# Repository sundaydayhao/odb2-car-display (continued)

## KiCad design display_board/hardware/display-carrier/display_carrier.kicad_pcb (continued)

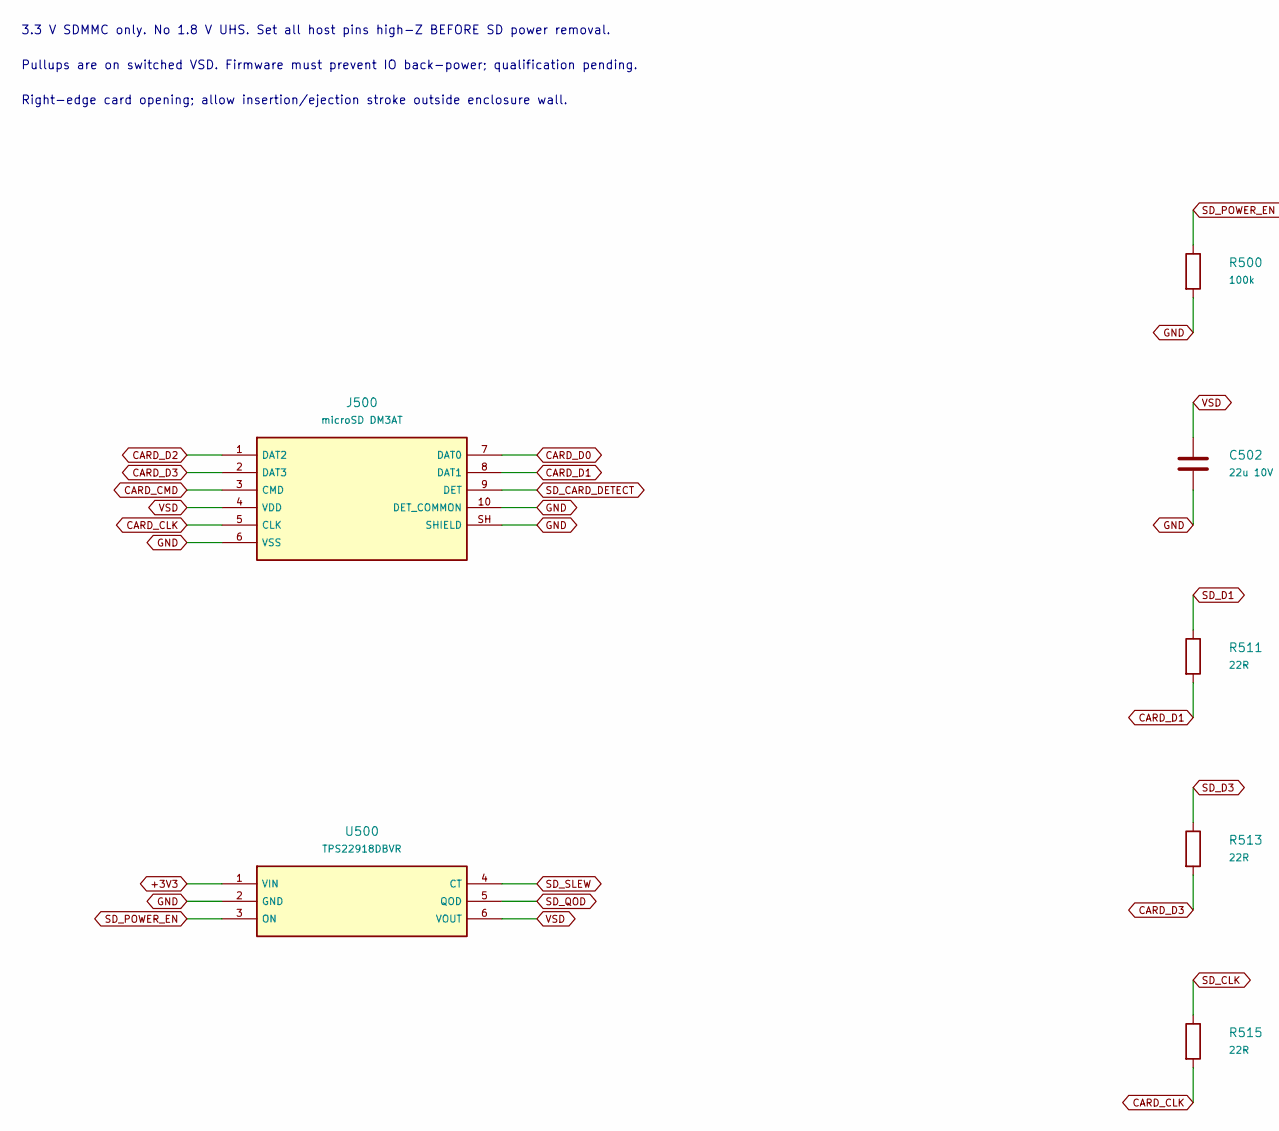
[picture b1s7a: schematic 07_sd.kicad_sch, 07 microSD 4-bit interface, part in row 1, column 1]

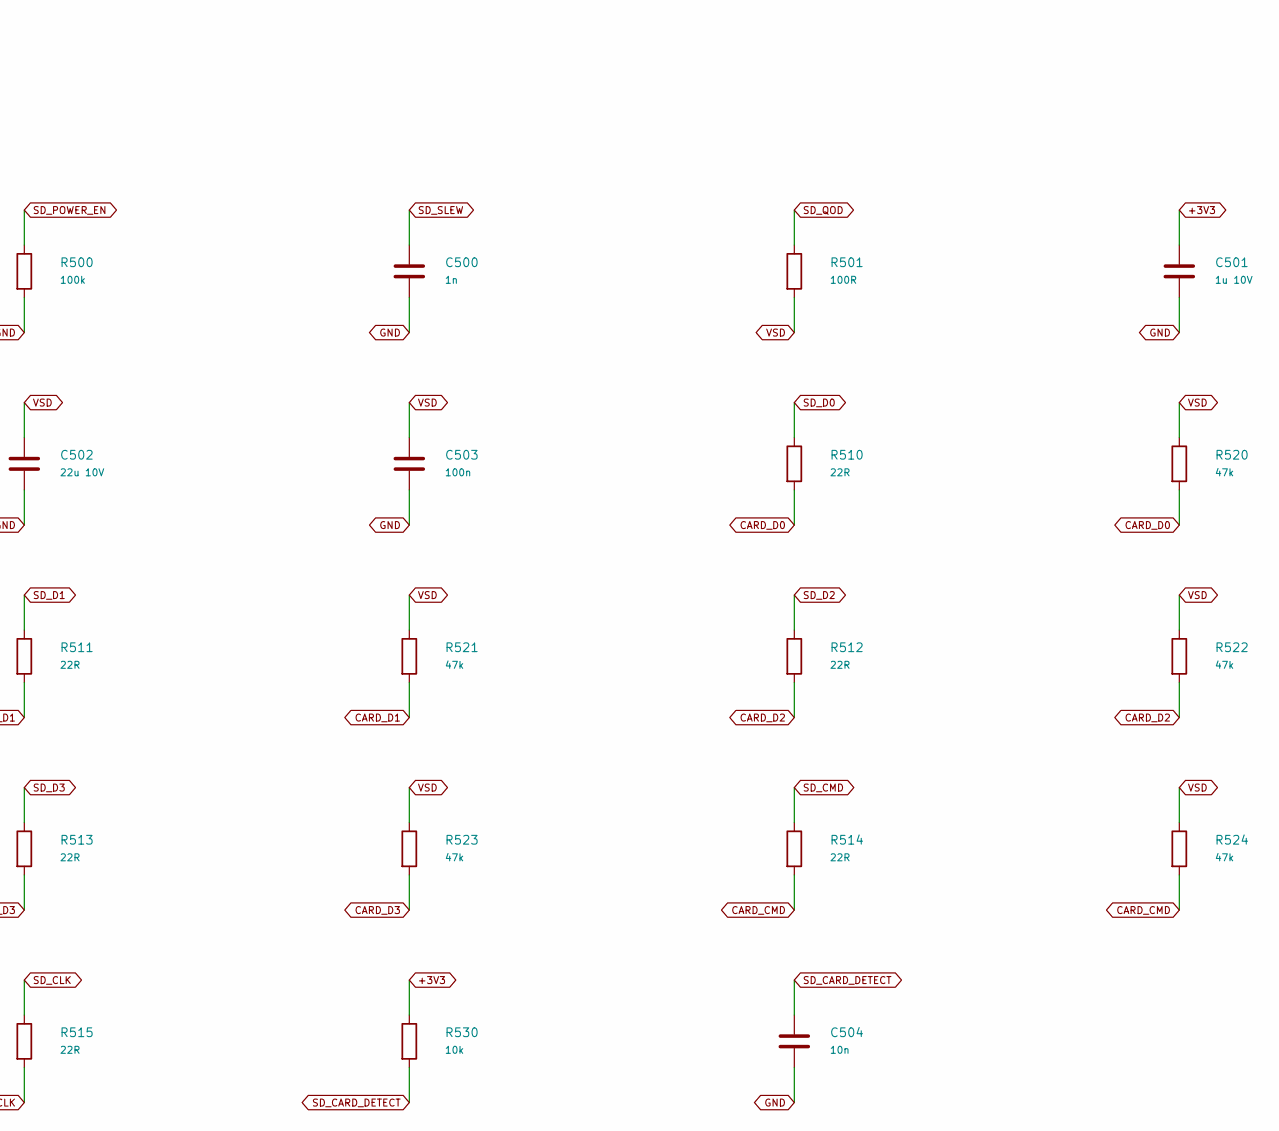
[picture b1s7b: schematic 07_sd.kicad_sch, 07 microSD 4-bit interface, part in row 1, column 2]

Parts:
C500: 1n; C_0402_1005Metric
C501: 1u 10V; C_0603_1608Metric
C502: 22u 10V; C_0805_2012Metric
C503: 100n; C_0402_1005Metric
C504: 10n; C_0603_1608Metric
J500: microSD DM3AT; microSD_HC_Hirose_DM3AT-SF-PEJM5
R500: 100k; R_0402_1005Metric
R501: 100R; R_0603_1608Metric
R510, R511, R512, R513, R514, R515: 22R; R_0402_1005Metric
R520, R521, R522, R523, R524: 47k; R_0402_1005Metric
R530: 10k; R_0402_1005Metric
U500: TPS22918DBVR; SOT-23-6

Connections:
+3V3: C501.1, R530.1, U500.1 (VIN); also elsewhere on the board
CARD_CLK: J500.5 (CLK), R515.2
CARD_CMD: J500.3 (CMD), R514.2, R524.2
CARD_D0: J500.7 (DAT0), R510.2, R520.2
CARD_D1: J500.8 (DAT1), R511.2, R521.2
CARD_D2: J500.1 (DAT2), R512.2, R522.2
CARD_D3: J500.2 (DAT3), R513.2, R523.2
GND: C500.2, C501.2, C502.2, C503.2, C504.2, J500.6 (VSS), J500.10 (DET_COMMON), J500.SH (SHIELD), R500.2, U500.2 (GND); also elsewhere on the board
SD_CARD_DETECT: C504.1, J500.9 (DET), R530.2; also elsewhere on the board
SD_CLK: R515.1; also elsewhere on the board
SD_CMD: R514.1; also elsewhere on the board
SD_D0: R510.1; also elsewhere on the board
SD_D1: R511.1; also elsewhere on the board
SD_D2: R512.1; also elsewhere on the board
SD_D3: R513.1; also elsewhere on the board
SD_POWER_EN: R500.1, U500.3 (ON); also elsewhere on the board
SD_QOD: R501.1, U500.5 (QOD)
SD_SLEW: C500.1, U500.4 (CT)
VSD: C502.1, C503.1, J500.4 (VDD), R501.2, R520.1, R521.1, R522.1, R523.1, R524.1, U500.6 (VOUT)

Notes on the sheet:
3.3 V SDMMC only. No 1.8 V UHS. Set all host pins high-Z BEFORE SD power removal.
Pullups are on switched VSD. Firmware must prevent IO back-power; qualification pending.
Right-edge card opening; allow insertion/ejection stroke outside enclosure wall.

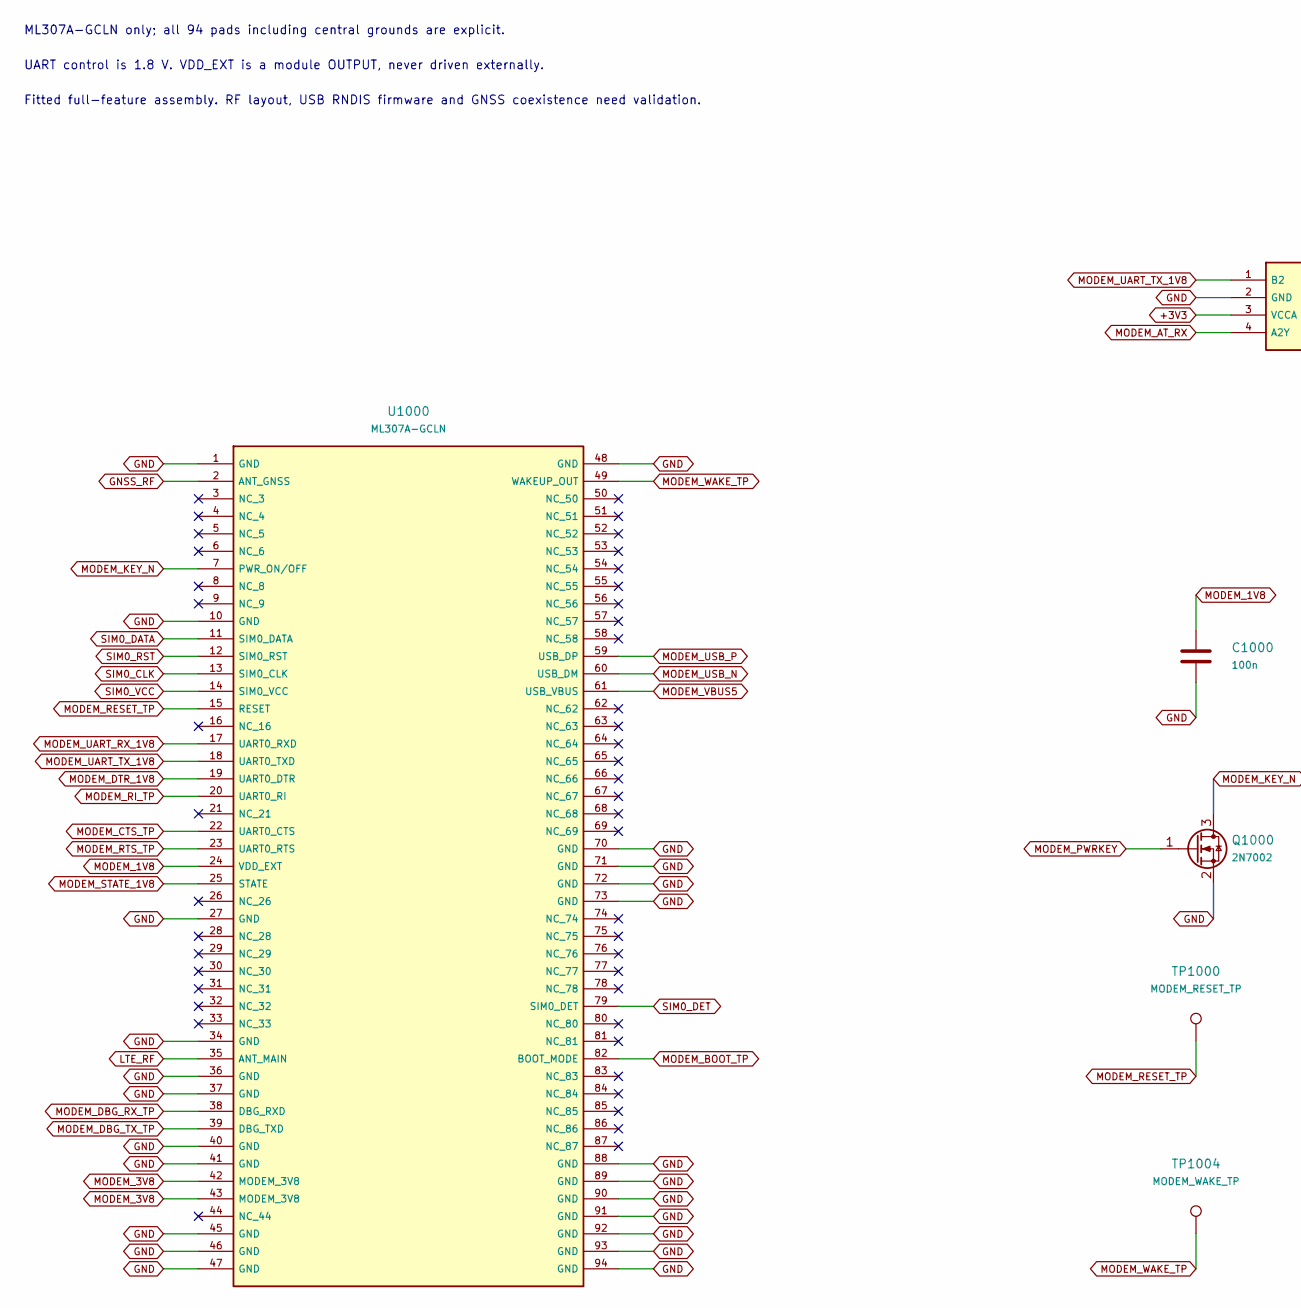
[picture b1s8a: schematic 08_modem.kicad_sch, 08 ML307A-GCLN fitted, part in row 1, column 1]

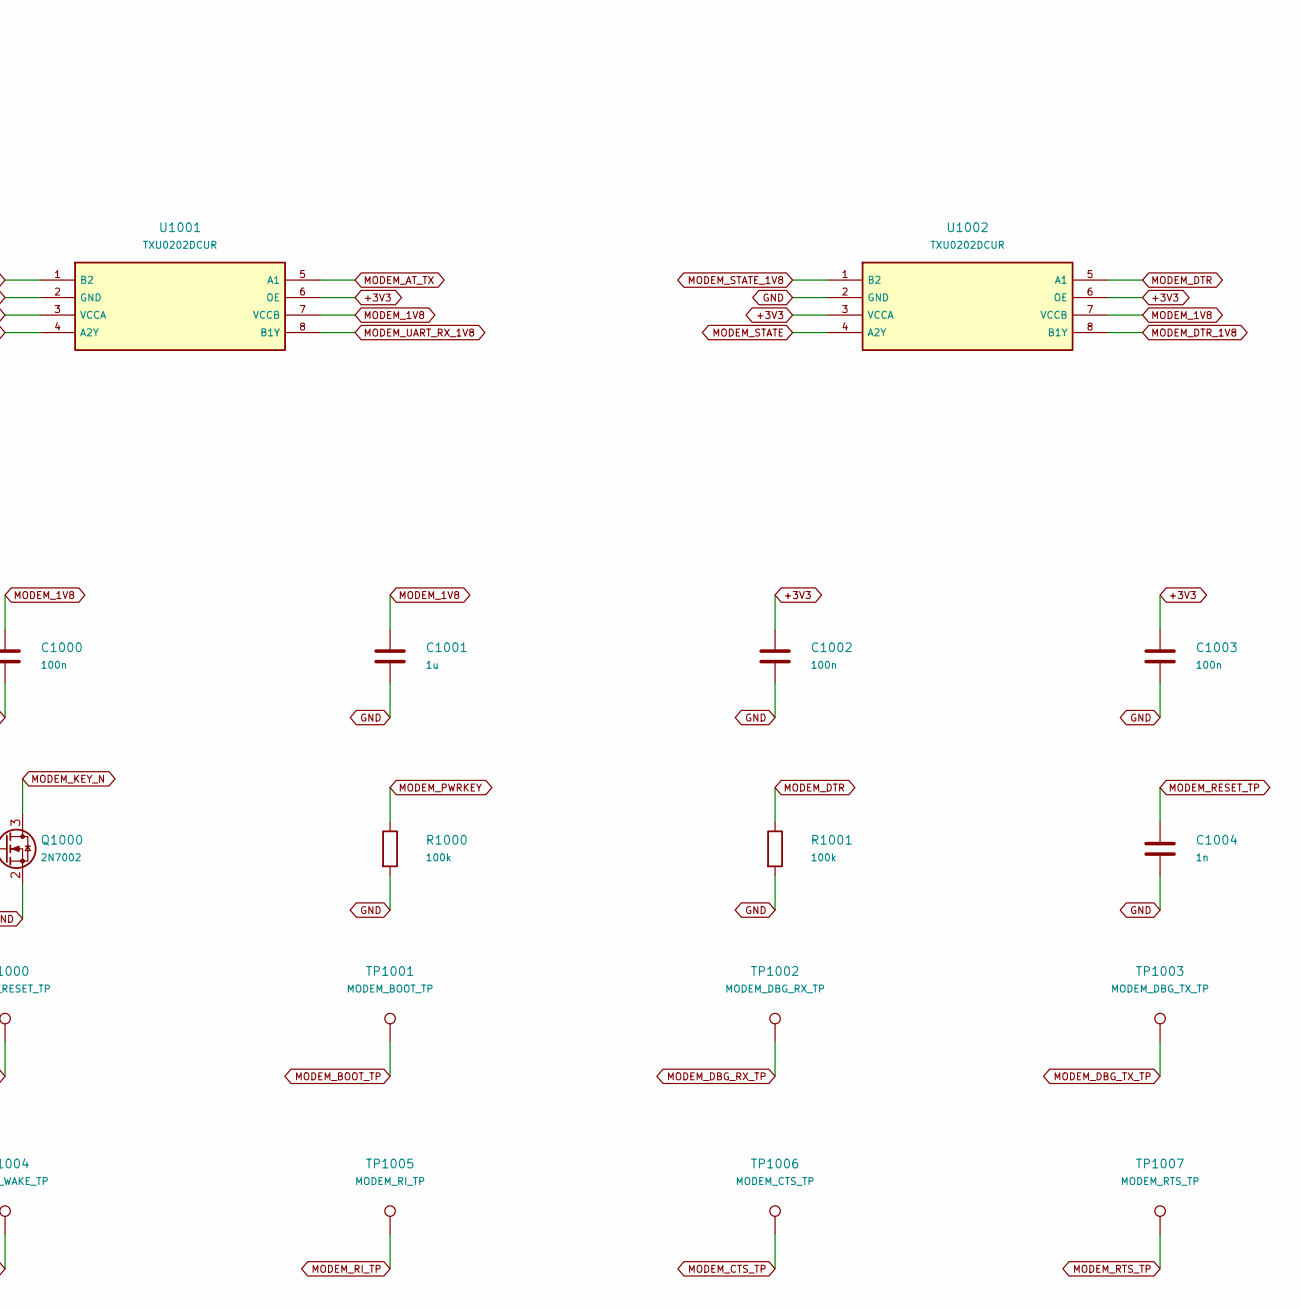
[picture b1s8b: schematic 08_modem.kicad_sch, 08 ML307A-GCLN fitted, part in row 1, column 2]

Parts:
C1000, C1002, C1003: 100n; C_0402_1005Metric
C1001: 1u; C_0603_1608Metric
C1004: 1n; C_0402_1005Metric
Q1000: 2N7002; SOT-23
R1000, R1001: 100k; R_0402_1005Metric
TP1000: MODEM_RESET_TP; TestPoint_Pad_D1.5mm
TP1001: MODEM_BOOT_TP; TestPoint_Pad_D1.5mm
TP1002: MODEM_DBG_RX_TP; TestPoint_Pad_D1.5mm
TP1003: MODEM_DBG_TX_TP; TestPoint_Pad_D1.5mm
TP1004: MODEM_WAKE_TP; TestPoint_Pad_D1.5mm
TP1005: MODEM_RI_TP; TestPoint_Pad_D1.5mm
TP1006: MODEM_CTS_TP; TestPoint_Pad_D1.5mm
TP1007: MODEM_RTS_TP; TestPoint_Pad_D1.5mm
U1000: ML307A-GCLN; ML307A_GCLN_LGA94
U1001, U1002: TXU0202DCUR; VSSOP-8_2.3x2mm_P0.5mm

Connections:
+3V3: C1002.1, C1003.1, U1001.3 (VCCA), U1001.6 (OE), U1002.3 (VCCA), U1002.6 (OE); also elsewhere on the board
GND: C1000.2, C1001.2, C1002.2, C1003.2, C1004.2, Q1000.2 (S), R1000.2, R1001.2, U1000.1 (GND), U1000.10 (GND), U1000.27 (GND), U1000.34 (GND), U1000.36 (GND), U1000.37 (GND), U1000.40 (GND), U1000.41 (GND), U1000.45 (GND), U1000.46 (GND), U1000.47 (GND), U1000.48 (GND), U1000.70 (GND), U1000.71 (GND), U1000.72 (GND), U1000.73 (GND), U1000.88 (GND), U1000.89 (GND), U1000.90 (GND), U1000.91 (GND), U1000.92 (GND), U1000.93 (GND), U1000.94 (GND), U1001.2 (GND), U1002.2 (GND); also elsewhere on the board
GNSS_RF: U1000.2 (ANT_GNSS); also elsewhere on the board
LTE_RF: U1000.35 (ANT_MAIN); also elsewhere on the board
MODEM_1V8: C1000.1, C1001.1, U1000.24 (VDD_EXT), U1001.7 (VCCB), U1002.7 (VCCB); also elsewhere on the board
MODEM_3V8: U1000.42 (MODEM_3V8), U1000.43 (MODEM_3V8); also elsewhere on the board
MODEM_AT_RX: U1001.4 (A2Y); also elsewhere on the board
MODEM_AT_TX: U1001.5 (A1); also elsewhere on the board
MODEM_BOOT_TP: TP1001.1, U1000.82 (BOOT_MODE)
MODEM_CTS_TP: TP1006.1, U1000.22 (UART0_CTS)
MODEM_DBG_RX_TP: TP1002.1, U1000.38 (DBG_RXD)
MODEM_DBG_TX_TP: TP1003.1, U1000.39 (DBG_TXD)
MODEM_DTR: R1001.1, U1002.5 (A1); also elsewhere on the board
MODEM_DTR_1V8: U1000.19 (UART0_DTR), U1002.8 (B1Y)
MODEM_KEY_N: Q1000.3 (D), U1000.7 (PWR_ON/OFF)
MODEM_PWRKEY: Q1000.1 (G), R1000.1; also elsewhere on the board
MODEM_RESET_TP: C1004.1, TP1000.1, U1000.15 (RESET)
MODEM_RI_TP: TP1005.1, U1000.20 (UART0_RI)
MODEM_RTS_TP: TP1007.1, U1000.23 (UART0_RTS)
MODEM_STATE: U1002.4 (A2Y); also elsewhere on the board
MODEM_STATE_1V8: U1000.25 (STATE), U1002.1 (B2)
MODEM_UART_RX_1V8: U1000.17 (UART0_RXD), U1001.8 (B1Y)
MODEM_UART_TX_1V8: U1000.18 (UART0_TXD), U1001.1 (B2)
MODEM_USB_N: U1000.60 (USB_DM); also elsewhere on the board
MODEM_USB_P: U1000.59 (USB_DP); also elsewhere on the board
MODEM_VBUS5: U1000.61 (USB_VBUS); also elsewhere on the board
MODEM_WAKE_TP: TP1004.1, U1000.49 (WAKEUP_OUT)
SIM0_CLK: U1000.13 (SIM0_CLK); also elsewhere on the board
SIM0_DATA: U1000.11 (SIM0_DATA); also elsewhere on the board
SIM0_DET: U1000.79 (SIM0_DET); also elsewhere on the board
SIM0_RST: U1000.12 (SIM0_RST); also elsewhere on the board
SIM0_VCC: U1000.14 (SIM0_VCC); also elsewhere on the board

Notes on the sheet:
ML307A-GCLN only; all 94 pads including central grounds are explicit.
UART control is 1.8 V. VDD_EXT is a module OUTPUT, never driven externally.
Fitted full-feature assembly. RF layout, USB RNDIS firmware and GNSS coexistence need validation.

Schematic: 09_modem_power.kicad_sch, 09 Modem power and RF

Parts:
C1010, C1011: 22u 10V; C_0805_2012Metric
C1012, C1013: 220u 6.3V polymer 15mR; KNSCHA_177EC0013_7343
C1014: 100n; C_0402_1005Metric
C1015: 100p C0G; C_0402_1005Metric
C1016: 33p C0G; C_0402_1005Metric
C1017: 1n; C_0402_1005Metric
C1018: 1u 10V; C_0603_1608Metric
C1019, C1020: 1u; C_0603_1608Metric
L1010: 1uH MWSA0402S-1R0MT; L_Sunlord_MWSA0402S
Q1010, Q1011: 2N7002; SOT-23
R1010: 536k 1%; R_0603_1608Metric
R1011: 100k 1%; R_0402_1005Metric
R1012, R1015, R1017: 100k; R_0402_1005Metric
R1013: 47k; R_0402_1005Metric
R1014: 100R 0.25W; R_1206_3216Metric
R1016: 1k; R_0603_1608Metric
TP1010: GNSS_A3V3; TestPoint_Pad_D1.5mm
TP1011: MODEM_3V8; TestPoint_Pad_D1.5mm
U1010: TLV62585DRLR; SOT-563
U1011: TPS22918DBVR; SOT-23-6
U1012: AP2112K-3.3TRG1; SOT-23-5

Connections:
+3V3: R1013.1; also elsewhere on the board
+5V: C1010.1, C1020.1, U1010.3 (VIN), U1011.1 (VIN), U1012.1 (VIN); also elsewhere on the board
GND: C1010.2, C1011.2, C1012.2, C1013.2, C1014.2, C1015.2, C1016.2, C1017.2, C1018.2, C1019.2, C1020.2, Q1010.2 (S), Q1011.2 (S), R1011.2, R1012.2, R1015.2, R1017.2, U1010.1 (GND), U1011.2 (GND), U1012.2 (GND); also elsewhere on the board
GNSS_A3V3: C1019.1, TP1010.1, U1012.5 (VOUT)
GNSS_ANT_POWER_EN: R1017.1, U1012.3 (EN); also elsewhere on the board
MODEM_3V8: C1011.1, C1012.1, C1013.1, C1014.1, C1015.1, C1016.1, L1010.2, R1010.1, R1014.1, TP1011.1; also elsewhere on the board
MODEM_DISCHARGE: Q1011.3 (D), R1014.2
MODEM_DISCHARGE_EN: Q1010.3 (D), Q1011.1 (G), R1013.2
MODEM_FB: R1010.2, R1011.1, U1010.5 (FB)
MODEM_POWER_EN: Q1010.1 (G), R1012.1, U1010.4 (EN); also elsewhere on the board
MODEM_SW: L1010.1, U1010.2 (SW)
MODEM_USB_QOD: R1016.1, U1011.5 (QOD)
MODEM_USB_SLEW: C1017.1, U1011.4 (CT)
MODEM_USB_VBUS_EN: R1015.1, U1011.3 (ON); also elsewhere on the board
MODEM_VBUS5: C1018.1, R1016.2, U1011.6 (VOUT); also elsewhere on the board

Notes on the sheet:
3.8 V / 2 A burst rail. 440 uF startup and RF burst droop MUST be measured.
USB VBUS detection and active-antenna bias are independently switched.
GNSS/LTE pi networks start at 0R series, shunt capacitors DNP; tune with enclosure/antenna.

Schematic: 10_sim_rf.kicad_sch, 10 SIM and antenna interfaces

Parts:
C1030: 1u 10V; C_0603_1608Metric
C1031: 10n; C_0603_1608Metric
C1040, C1041, C1042, C1043: DNP RF tune; C_0603_1608Metric; not fitted
C1044: 100p C0G RF DC block; C_0402_1005Metric
J1000: GCT SIM8066-6-1-14-01-A; nanoSIM_GCT_SIM8066_PushPush
J1010, J1011: U.FL-R-SMT-1(80); U.FL_Hirose_U.FL-R-SMT-1_Vertical
R1030, R1031, R1032: 22R; R_0402_1005Metric
R1033, R1034: 10k; R_0402_1005Metric
R1040: 0R RF match; R_0603_1608Metric
U1030, U1031: USBLC6-2SC6; SOT-23-6

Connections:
GND: C1030.2, C1031.2, C1040.2, C1041.2, C1042.2, C1043.2, J1000.5 (GND), J1000.SH (SHIELD), J1010.2 (GND), J1011.2 (GND), U1030.2 (GND), U1031.2 (GND), U1031.3 (I/O2), U1031.4 (I/O2); also elsewhere on the board
GNSS_ANT: C1043.1, C1044.2, J1011.1 (RF)
GNSS_RF: C1042.1, C1044.1; also elsewhere on the board
LTE_ANT: C1041.1, J1010.1 (RF), R1040.2
LTE_RF: C1040.1, R1040.1; also elsewhere on the board
MODEM_1V8: R1033.1; also elsewhere on the board
SIM0_CLK: R1032.1; also elsewhere on the board
SIM0_DATA: R1030.1; also elsewhere on the board
SIM0_DET: C1031.1, J1000.SW (DETECT), R1033.2; also elsewhere on the board
SIM0_RST: R1031.1; also elsewhere on the board
SIM0_VCC: C1030.1, J1000.1 (VCC), R1034.1, U1030.5 (VBUS), U1031.5 (VBUS); also elsewhere on the board
SIM_CLK_SOCKET: J1000.3 (CLK), R1032.2, U1030.3 (I/O2), U1030.4 (I/O2)
SIM_DATA_SOCKET: J1000.7 (DATA), R1030.2, R1034.2, U1030.1 (I/O1), U1030.6 (I/O1)
SIM_RST_SOCKET: J1000.2 (RST), R1031.2, U1031.1 (I/O1), U1031.6 (I/O1)

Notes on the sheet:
SIM voltage is supplied by modem. Do not connect 3.3 V to SIM0_VCC.
J1000 SIM8066 push-push: side insertion and press-to-eject. CD-GND closed without card, open with card.
SIM0_DET HIGH = card present, LOW = absent, matching ML307A default. 10k pull-up to MODEM_1V8.
RF traces require 50 ohm controlled impedance and antenna matching validation.
GNSS connector is DC-blocked. Active-antenna bias is a separate release hold.

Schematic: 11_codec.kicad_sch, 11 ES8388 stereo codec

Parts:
C800, C808, C809, C810, C811: 1u 10V; C_0603_1608Metric
C801, C806, C807, C880: 10u 10V; C_0603_1608Metric
C802, C803, C804, C805, C879, C881, C882: 100n 10V; C_0402_1005Metric
R800, R801, R802, R803, R804: 22R; R_0402_1005Metric
R805, R806, R807, R808, R809, R810: 100k; R_0402_1005Metric
U800: ES8388; ES8388_QFN28_4x4_P0.45
U801: AP2112K-3.3TRG1; SOT-23-5

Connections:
+5V: C800.1, U801.1 (VIN), U801.3 (EN); also elsewhere on the board
ADC_VREF: C806.1, C881.1, U800.19 (ADCVREF)
AUDIO_3V3: C801.1, C802.1, C803.1, C804.1, C879.1, C880.1, U800.2 (DVDD), U800.3 (PVDD), U800.16 (HPVDD), U800.17 (AVDD), U801.5 (VOUT); also elsewhere on the board
AUDIO_MID: R807.1, R808.1, R809.1, R810.1; also elsewhere on the board
CODEC_AD0: R805.1, U800.26 (CE)
CODEC_BCLK: R801.2, U800.5 (SCLK)
CODEC_DOUT: R804.1, R806.1, U800.8 (ASDOUT)
CODEC_LRCK: R802.2, U800.7 (LRCK)
CODEC_MCLK: R800.2, U800.1 (MCLK)
CODEC_TDMIN: R803.2, U800.6 (DSDIN)
CODEC_VMID: C807.1, C882.1, U800.20 (VMID)
DAC_L_N_AC: C809.2, R808.2; also elsewhere on the board
DAC_L_P: C808.1, U800.12 (LOUT1)
DAC_L_P_AC: C808.2, R807.2; also elsewhere on the board
DAC_R_N_AC: C811.2, R810.2; also elsewhere on the board
DAC_R_P: C810.1, U800.11 (ROUT1)
DAC_R_P_AC: C810.2, R809.2; also elsewhere on the board
DAC_VREF: C805.1, U800.10 (VREF)
GND: C800.2, C801.2, C802.2, C803.2, C804.2, C805.2, C806.2, C807.2, C809.1, C811.1, C879.2, C880.2, C881.2, C882.2, R805.2, R806.2, U800.4 (DGND), U800.13 (HPGND), U800.18 (AGND), U800.29 (EP), U801.2 (GND); also elsewhere on the board
I2S_BCLK: R801.1; also elsewhere on the board
I2S_DIN: R804.2; also elsewhere on the board
I2S_DOUT: R803.1; also elsewhere on the board
I2S_LRCK: R802.1; also elsewhere on the board
I2S_MCLK: R800.1; also elsewhere on the board
MIC_L_N: U800.23 (RIN1); also elsewhere on the board
MIC_L_P: U800.24 (LIN1); also elsewhere on the board
MIC_R_N: U800.21 (RIN2); also elsewhere on the board
MIC_R_P: U800.22 (LIN2); also elsewhere on the board
SYSTEM_I2C_SCL: U800.28 (CCLK); also elsewhere on the board
SYSTEM_I2C_SDA: U800.27 (CDATA); also elsewhere on the board

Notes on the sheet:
ES8388 QFN28 replaces ES8389. 0x10 I2C; standard I2S slave on existing GPIO9..13.
Dual differential ADC: LIN1-RIN1=left mic; LIN2-RIN2=right mic. Reg10=0xFC, Reg11.DS=0.
LOUT1/ROUT1 feed the stereo line path. Negative PA inputs have AC ground returns; unused OUT2 pins are NC.
No ES8389 TDM pin swap or 192kHz support. Port ES8388 initialization; mute PAs during transitions.

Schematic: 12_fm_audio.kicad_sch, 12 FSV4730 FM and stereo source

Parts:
C812, C813: 1u 10V; C_0603_1608Metric
C814: 22n; C_0402_1005Metric
C815, C816: 2.2u 10V; C_0603_1608Metric
C817: 10u 10V; C_0805_2012Metric
C818, C819, C820, C821: 100n; C_0402_1005Metric
C822: 1n C0G; C_0603_1608Metric
C823, C827: 100n 10V; C_0402_1005Metric
C824: 470n 25V; C_0603_1608Metric
C825, C826: 22p C0G; C_0402_1005Metric
D810: PESD5V0U1BA; D_SOD-323
J810: FM ANT / GND; JST_PH_B2B-PH-K_1x02_P2.00mm_Vertical
Q810, Q811: 2N7002; SOT-23
R811, R812, R815, R816, R820: 100k; R_0402_1005Metric
R813, R814: 4.7k; R_0402_1005Metric
R817, R818, R821: 10k; R_0402_1005Metric
R819: 1k; R_0603_1608Metric
U810: ME6211C30M5G-N; SOT-23-5
U811, U812, U813, U814: SN74LVC1G3157DCKR; SOT-363_SC-70-6
U815: FSV4730-D60-GU; FSV4730_SSOP24
U816: MCP120T-270I/TT; SOT23_MCP120
Y810: SXTF3215R32768A20F; SXTF3215R_32k

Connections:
AMP_L_N_AC: U812.4 (A); also elsewhere on the board
AMP_L_P_AC: U811.4 (A); also elsewhere on the board
AMP_R_N_AC: U814.4 (A); also elsewhere on the board
AMP_R_P_AC: U813.4 (A); also elsewhere on the board
AUDIO_3V3: C812.1, C818.1, C819.1, C820.1, C821.1, R817.1, U810.1 (VIN), U811.5 (VCC), U812.5 (VCC), U813.5 (VCC), U814.5 (VCC); also elsewhere on the board
AUDIO_MID: C817.1, R815.1, R816.1, R817.2, R818.1, U812.1 (B2), U814.1 (B2); also elsewhere on the board
AUDIO_SELECT_LOCAL: R819.2, R820.1, U811.6 (S), U812.6 (S), U813.6 (S), U814.6 (S)
AUDIO_SOURCE_SELECT: R819.1; also elsewhere on the board
DAC_L_N_AC: U812.3 (B1); also elsewhere on the board
DAC_L_P_AC: U811.3 (B1); also elsewhere on the board
DAC_R_N_AC: U814.3 (B1); also elsewhere on the board
DAC_R_P_AC: U813.3 (B1); also elsewhere on the board
FM_3V0: C813.1, C814.1, C823.1, C827.1, Q810.1 (G), Q811.1 (G), R811.1, R813.1, R814.1, R821.1, U810.5 (VOUT), U815.20 (VD), U815.21 (VA), U816.2 (VDD)
FM_ANT: C822.1, D810.1 (A1), J810.1
FM_ANT_IN: C822.2, U815.8 (FMI)
FM_DBYP: C824.1, U815.22 (DBYP)
FM_L: C815.1, U815.24 (LOUT)
FM_L_BIASED: C815.2, R815.2, U811.1 (B2)
FM_POWER_EN: R812.1, U810.3 (CE); also elsewhere on the board
FM_R: C816.1, U815.23 (ROUT)
FM_RCLK: C825.1, U815.19 (RCLK), Y810.1 (X1)
FM_RESET_N: R821.2, U815.15 (RST_N), U816.1 (RESET_N)
FM_R_BIASED: C816.2, R816.2, U813.1 (B2)
FM_SCL: Q811.2 (S), R814.2, U815.17 (SCLK)
FM_SDA: Q810.2 (S), R813.2, U815.18 (SDIO)
FM_XTAL_OUT: C826.1, U815.3 (GPO3_XTAL), Y810.2 (X2)
GND: C812.2, C813.2, C814.2, C817.2, C818.2, C819.2, C820.2, C821.2, C823.2, C824.2, C825.2, C826.2, C827.2, D810.2 (A2), J810.2, R811.2, R812.2, R818.2, R820.2, U810.2 (VSS), U811.2 (GND), U812.2 (GND), U813.2 (GND), U814.2 (GND), U815.2 (DFS), U815.9 (RFGND), U815.10 (GND_RESERVED1), U815.11 (GND_RESERVED2), U815.12 (AMI), U815.13 (GND1), U815.14 (GND2), U815.16 (SEN), U816.3 (VSS); also elsewhere on the board
SYSTEM_I2C_SCL: Q811.3 (D); also elsewhere on the board
SYSTEM_I2C_SDA: Q810.3 (D); also elsewhere on the board

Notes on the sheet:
Onboard FSV4730-D60-GU replaces unavailable RDA5807M; analog FM stereo, 64..108MHz; no RDS.
SEN=GND selects 0x11; ES8388=0x10, OPT3001=0x45, SHT40=0x44: no I2C address collision.
MCP120 delays reset release (700ms max). Hold system I2C idle for 1s after enabling FM power, then poll CTS.
Crystal connects RCLK to GPO3, with 22pF loads. Firmware enables crystal mode; unused AM input grounded.
Existing independent stereo selector and antenna ESD retained. Port FM driver and verify RF on hardware.

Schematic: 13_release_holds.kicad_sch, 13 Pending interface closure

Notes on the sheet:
NOT IMPLEMENTED: LCD bias/backlight, camera power/clock/level conversion and their support circuits.
LCD: vendor 2-lane initialization / legal timing required; FPC contact side and mechanical mating still need verification.
FPC sockets J1200/J1210/J1220 are fitted on F side. Touch pinout and folded LCD fit are not verified.
GNSS: passive RF path drawn. Active antenna current-limit/bias feed is not implemented.
BATTERY: hardware 0..45C cutoff, reverse connection, exact pack/NTC/fuse still need closure.
FPC adjustment areas are mechanical notes; they are not proof of cable reach or finished circuits.
Do not fabricate or call this a commercial-ready design. See DESIGN_STATUS.md for next gates.

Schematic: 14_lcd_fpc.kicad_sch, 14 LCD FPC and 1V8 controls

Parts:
C1200, C1201: 1u 10V X7R; C_0603_1608Metric
C1202, C1203: 100n 10V X7R; C_0402_1005Metric
J1200: FPC-05FB-30PH20; XUNPU_FPC_05FB_30PH20
R1200, R1202, R1203, R1204, R1205: 100k; R_0402_1005Metric
R1201: 10k bleed; R_0402_1005Metric
R1206, R1207: 10k scan option; R_0402_1005Metric
U1200: AP2112K-1.8TRG1; SOT-23-5
U1201: TXU0102DCUR; VSSOP-8_2.3x2mm_P0.5mm

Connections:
+3V3: C1200.1, C1203.1, U1200.1 (VIN), U1201.3 (VCCA); also elsewhere on the board
DSI_CLK_N: J1200.18 (DSI_CLK_N); also elsewhere on the board
DSI_CLK_P: J1200.17 (DSI_CLK_P); also elsewhere on the board
DSI_D0_N: J1200.24 (DSI_D0_N); also elsewhere on the board
DSI_D0_P: J1200.23 (DSI_D0_P); also elsewhere on the board
DSI_D1_N: J1200.21 (DSI_D1_N); also elsewhere on the board
DSI_D1_P: J1200.20 (DSI_D1_P); also elsewhere on the board
GND: C1200.2, C1201.2, C1202.2, C1203.2, J1200.10 (GND), J1200.13 (GND), J1200.16 (GND), J1200.19 (GND), J1200.22 (GND), J1200.25 (GND), J1200.MP (MOUNT), R1200.2, R1201.2, R1202.2, R1203.2, R1204.2, R1205.2, R1207.2, U1200.2 (GND), U1201.2 (GND); also elsewhere on the board
LCD_1V8: C1201.1, C1202.1, J1200.28 (VDD_1V8), J1200.29 (VDD_1V8), R1201.1, R1206.2, U1200.5 (VOUT), U1201.6 (OE), U1201.7 (VCCB)
LCD_AVDD_9V8: J1200.9 (AVDD)
LCD_LEDA: J1200.1 (LEDA), J1200.2 (LEDA)
LCD_LEDK: J1200.7 (LEDK), J1200.8 (LEDK)
LCD_RESET: R1202.1, U1201.5 (A1); also elsewhere on the board
LCD_RESET_1V8: J1200.27 (RESET_1V8), R1204.1, U1201.8 (B1Y)
LCD_SHLR: J1200.6 (SHLR), R1207.1
LCD_STBYB: R1203.1, U1201.4 (A2); also elsewhere on the board
LCD_STBYB_1V8: J1200.26 (STBYB_1V8), R1205.1, U1201.1 (B2Y)
LCD_UPDN: J1200.5 (UPDN), R1206.1
LCD_VCOM: J1200.30 (VCOM)
LCD_VDD_EN: R1200.1, U1200.3 (EN); also elsewhere on the board
LCD_VGH: J1200.3 (VGH)
LCD_VGL: J1200.4 (VGL)

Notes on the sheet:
J1200: 30-pin / 0.5 mm; F faces rear housing. Screen is on B; cable passes through a routed slot.
Only D0/D1 are connected. Vendor 2-lane initialization and timing remain REQUIRED.
LCD_AVDD_9V8 / VGH / VGL / VCOM and LEDA/K are UNDRIVEN: bias/backlight stage still pending.
Slot and connector positions are provisional: verify 3D flex reach, pin-1, thickness and screen spacing.

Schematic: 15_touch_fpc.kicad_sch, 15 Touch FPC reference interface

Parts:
C1210: 100n 10V X7R; C_0402_1005Metric
C1211: 1u 10V X7R; C_0603_1608Metric
J1210: FPC-05FB-6PH20; XUNPU_FPC_05FB_6PH20
R1210, R1211, R1212, R1213: 100R; R_0402_1005Metric
R1214, R1215: 4.7k; R_0402_1005Metric

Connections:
+3V3: C1210.1, C1211.1, J1210.2 (VCC_3V3), R1214.1, R1215.1; also elsewhere on the board
CAM_TOUCH_I2C_SCL: R1213.1, R1215.2; also elsewhere on the board
CAM_TOUCH_I2C_SDA: R1212.1, R1214.2; also elsewhere on the board
GND: C1210.2, C1211.2, J1210.3 (GND), J1210.MP (MOUNT); also elsewhere on the board
TOUCH_INT: R1211.1; also elsewhere on the board
TOUCH_INT_CONN: J1210.4 (INT), R1211.2
TOUCH_RESET: R1210.1; also elsewhere on the board
TOUCH_RESET_CONN: J1210.1 (RESET_CONTROL), R1210.2
TOUCH_SCL_CONN: J1210.6 (SCL), R1213.2
TOUCH_SDA_CONN: J1210.5 (SDA), R1212.2

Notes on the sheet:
J1210: 6-pin reference interface; selected touch module drawing has NOT been supplied.
1 RESET/control, 2 3V3, 3 GND, 4 INT, 5 SDA, 6 SCL. Verify all six before plugging in.
F faces rear housing; screen flex passes from B through a slot. Same entry direction as LCD.
3V3 interface assumption only; contact width/thickness, voltage, polarity and ESD await closure.

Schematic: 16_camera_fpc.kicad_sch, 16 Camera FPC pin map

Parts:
J1220: FPC-05FB-24PH20; XUNPU_FPC_05FB_24PH20

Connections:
CAM_AVDD_2V8: J1220.23 (AVDD_2V8), J1220.24 (AVDD_2V8)
CAM_DOVDD_1V8: J1220.16 (DOVDD_1V8)
CAM_MCLK_1V8: J1220.14 (MCLK_1V8)
CAM_RESET_1V8: J1220.17 (RESET_1V8)
CAM_SCL_1V8: J1220.21 (SCL_1V8)
CAM_SDA_1V8: J1220.20 (SDA_1V8)
CSI_CLK_N: J1220.6 (CLK_N); also elsewhere on the board
CSI_CLK_P: J1220.7 (CLK_P); also elsewhere on the board
CSI_D0_N: J1220.9 (D0_N); also elsewhere on the board
CSI_D0_P: J1220.10 (D0_P); also elsewhere on the board
CSI_D1_N: J1220.3 (D1_N); also elsewhere on the board
CSI_D1_P: J1220.4 (D1_P); also elsewhere on the board
GND: J1220.5 (GND), J1220.8 (GND), J1220.13 (GND), J1220.15 (GND), J1220.19 (GND), J1220.22 (GND), J1220.MP (MOUNT); also elsewhere on the board

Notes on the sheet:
J1220: OSPTEK ESP32-P4-Camera SC2336 specification p3, 24 pins / 0.5 mm / 0.3 mm tail.
CSI pairs connected to core. 1V8 / 2V8 supplies, sequencer, 24MHz and level conversion PENDING.
CAM_*_1V8 labels are isolated interface boundaries: NEVER bridge them straight to 3V3 GPIO.
Pins 1/2/11/12/18 stay NC. No external 1V5 pin exists in this module pin map.

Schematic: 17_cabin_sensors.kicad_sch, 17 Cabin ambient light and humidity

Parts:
C1300, C1301: 100n 10V X7R; C_0402_1005Metric
C1302: 1u 10V X7R; C_0603_1608Metric
R1300, R1301: 22R; R_0402_1005Metric
U1300: OPT3001DNPR; OPT3001_DNP0006A
U1301: SHT40-AD1B-R2; SHT40_DFN4_NoCentralPad

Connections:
+3V3: C1300.1, C1301.1, C1302.1, U1300.1 (VDD), U1300.2 (ADDR), U1301.3 (VDD); also elsewhere on the board
CABIN_I2C_SCL: R1301.2, U1300.4 (SCL), U1301.2 (SCL)
CABIN_I2C_SDA: R1300.2, U1300.6 (SDA), U1301.1 (SDA)
GND: C1300.2, C1301.2, C1302.2, U1300.3 (GND), U1300.7 (EP_GND), U1301.4 (VSS); also elsewhere on the board
SYSTEM_I2C_SCL: R1301.1; also elsewhere on the board
SYSTEM_I2C_SDA: R1300.1; also elsewhere on the board

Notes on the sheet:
OPT3001DNPR: ADDR=3V3 selects 0x45; SHT40-AD1B-R2 fixed 0x44. SYSTEM_I2C, no extra GPIO.
Reuse R110/R111 4.7k bus pull-ups. R1300/R1301 are 22R branch damping; start at 100kHz.
U1300 needs a housing optical window/light guide and LCD stray-light baffle; calibrate assembled optics.
U1301 needs a vented isolated pocket, PCB thermal slots and no copper pour. Heater OFF for cabin readings.
These are populated sensor circuits; housing response, optical calibration and firmware are unvalidated.

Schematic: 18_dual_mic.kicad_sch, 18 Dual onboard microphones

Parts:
C840, C841, C842, C844, C845, C846: 1u 10V; C_0603_1608Metric
C843, C847: 100p C0G; C_0402_1005Metric
C848, C849: 100n 10V; C_0402_1005Metric
R840, R841: 100R; R_0402_1005Metric
U802, U803: LMA3729T381-OAS02; LMA3729T381_OAS02_TopPort

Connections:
AUDIO_3V3: R840.1, R841.1; also elsewhere on the board
GND: C840.2, C842.1, C844.2, C846.1, C848.2, C849.2, U802.3 (GND1), U802.4 (GND2), U803.3 (GND1), U803.4 (GND2); also elsewhere on the board
MIC_L_3V3: C840.1, C848.1, R840.2, U802.1 (VDD)
MIC_L_N: C842.2, C843.2; also elsewhere on the board
MIC_L_OUT: C841.1, U802.2 (OUT)
MIC_L_P: C841.2, C843.1; also elsewhere on the board
MIC_R_3V3: C844.1, C849.1, R841.2, U803.1 (VDD)
MIC_R_N: C846.2, C847.2; also elsewhere on the board
MIC_R_OUT: C845.1, U803.2 (OUT)
MIC_R_P: C845.2, C847.1; also elsewhere on the board

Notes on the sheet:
Two LMA3729T381-OAS02 top-port MEMS microphones solder directly to the F face, toward rear housing.
U802=left, U803=right. Same part/orientation; 131mm nominal center spacing, two separate housing ports.
Codec senses each microphone OUT against its local ground via a matched AC-coupled pair.
Keep acoustic ports clear of solder paste, adhesive and coating; no board washing or ultrasonic cleaning.

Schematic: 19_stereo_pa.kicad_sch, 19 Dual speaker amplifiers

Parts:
C860, C861, C863, C868, C869, C871: 100n 10V; C_0402_1005Metric
C862, C870: 1u 10V; C_0603_1608Metric
C864, C872: 10u 10V; C_0805_2012Metric
C865, C866, C873, C874: 1n C0G; C_0603_1608Metric
C876, C877, C878: 22u 10V; C_0805_2012Metric
J820: SPEAKER L / 4R; JST_PH_B2B-PH-K_1x02_P2.00mm_Vertical
J821: SPEAKER R / 4R; JST_PH_B2B-PH-K_1x02_P2.00mm_Vertical
L820: 1uH MWSA0402S-1R0MT; L_Sunlord_MWSA0402S
R860, R861, R863, R864, R867: 100k 1%; R_0402_1005Metric
R862, R865: 10k; R_0402_1005Metric
R866: 680k 1%; R_0603_1608Metric
U820, U821: NS4150B; MSOP-8_3x3mm_P0.65mm
U822: TLV62585DRLR; SOT-563

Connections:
+5V: C876.1, U822.3 (VIN), U822.4 (EN); also elsewhere on the board
AMP_EN: R862.1, R865.1, U820.1 (CTRL), U821.1 (CTRL); also elsewhere on the board
AMP_L_N_AC: C861.1; also elsewhere on the board
AMP_L_P_AC: C860.1; also elsewhere on the board
AMP_R_N_AC: C869.1; also elsewhere on the board
AMP_R_P_AC: C868.1; also elsewhere on the board
GND: C862.2, C863.2, C864.2, C865.2, C866.2, C870.2, C871.2, C872.2, C873.2, C874.2, C876.2, C877.2, C878.2, R862.2, R865.2, R867.2, U820.7 (GND), U821.7 (GND), U822.1 (GND); also elsewhere on the board
PA_4V8: C863.1, C864.1, C871.1, C872.1, C877.1, C878.1, L820.2, R866.1, U820.6 (VCC), U821.6 (VCC)
PA_BUCK_FB: R866.2, R867.1, U822.5 (FB)
PA_BUCK_SW: L820.1, U822.2 (SW)
PA_L_BYPASS: C862.1, U820.2 (BYPASS)
PA_L_CIN_N: C861.2, R861.1
PA_L_CIN_P: C860.2, R860.1
PA_L_INN: R861.2, U820.4 (INN)
PA_L_INP: R860.2, U820.3 (INP)
PA_R_BYPASS: C870.1, U821.2 (BYPASS)
PA_R_CIN_N: C869.2, R864.1
PA_R_CIN_P: C868.2, R863.1
PA_R_INN: R864.2, U821.4 (INN)
PA_R_INP: R863.2, U821.3 (INP)
SPK_L_N: C866.1, J820.2, U820.5 (VON)
SPK_L_P: C865.1, J820.1, U820.8 (VOP)
SPK_R_N: C874.1, J821.2, U821.5 (VON)
SPK_R_P: C873.1, J821.1, U821.8 (VOP)

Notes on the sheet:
S31-Korvo-1 dual NS4150B structure. J820/J821 are independent BTL outputs; neither terminal is GND.
Separate 4.68V buck rail (legacy net PA_4V8) stays below 5V across static tolerance; see procurement audit.
100k input resistors: nominal differential gain 240k/100k=2.4 (7.6dB). Start volume low.
AMP_EN low mutes both channels; assert only after rail/codec settle. No 5W or simultaneous full-load claim.

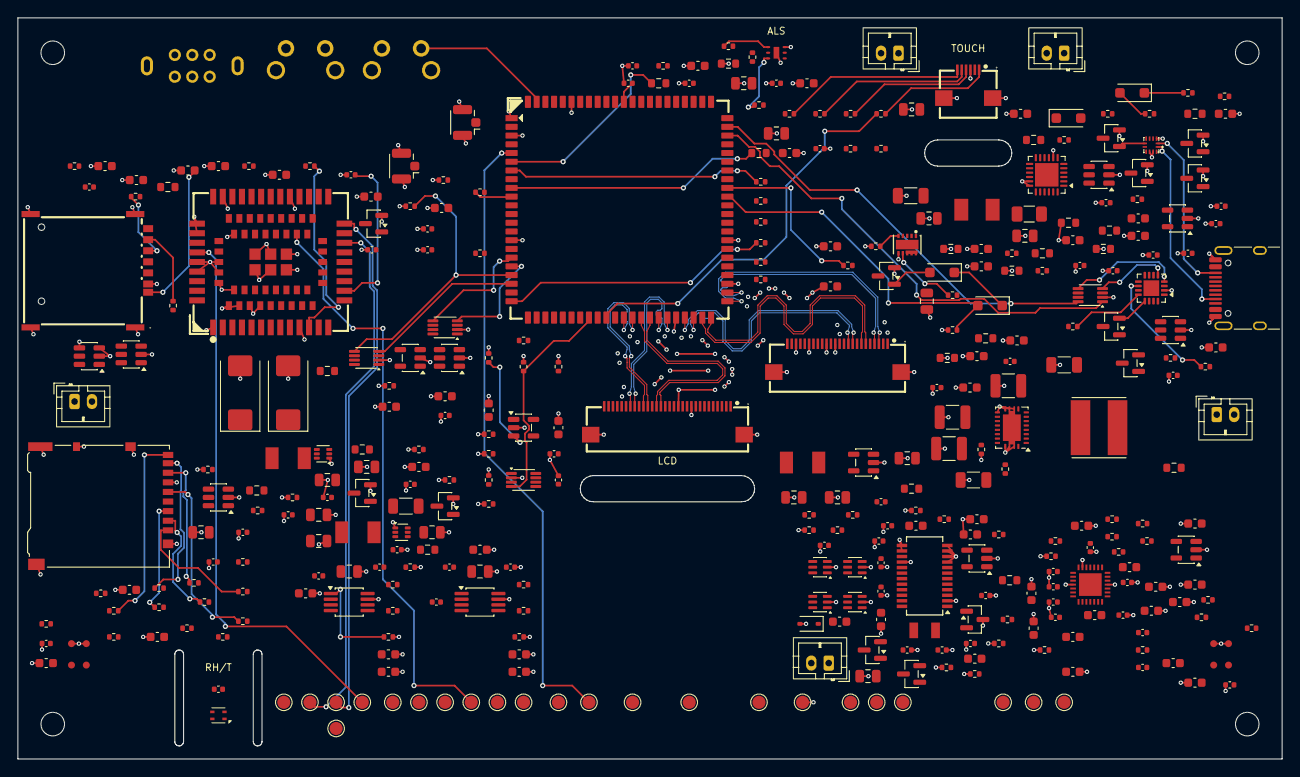
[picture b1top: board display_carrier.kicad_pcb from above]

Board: 4 copper layers, 145.0 x 85.0 mm, 365 parts (0 on the bottom side), 238 nets.

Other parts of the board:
H1, H2, H3, H4: M2.5 NPTH; MountingHole_2.7mm_M2.5
